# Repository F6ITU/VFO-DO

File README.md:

VFO-DO
RF Generator, Kicad project

VFO-DO est un générateur HF couvrant de quelques kHz à 100 MHz.

Il s'agit d'une idée originale de Gene Marcus W3PM/GM4YRE
publiée dans un article de la revue QEX

http://www.arrl.org/files/file/QEX_Next_Issue/2015/Jul-Aug_2015/Marcus.pdf

Ce projet Kicad n'est que la transposition dudit projet. 

La propriété intellectuelle et les droits de publication appartiennent respectivement 
à l'auteur et à la société de publication mentionnés

Ce projet Kicad poursuit deux buts : 

- offrir à chaque débutant en électronique ou en radioélectricité les éléments nécessaires
à la construction d'une source de fréquence excessivement stable (précise au Herz près, puisque pilotée par l'étalon césium
de l'essaim de satellites GPS)... et surtout simple à construire -à assembler serait le terme le plus exact.

- étendre cette réalisation, après modification du firmware, avec un filtre 

https://github.com/F6ITU/FiltreU

commuté de 8 bandes 

https://github.com/F6ITU/octorelay

qui éliminera en grande partie les harmoniques du générateur -lequel génère des signaux carrés-

De cette manière, la pureté spectrale est largement suffisante pour satisfaire la majorité des 
débutants en électronique "haute fréquence"

Le filtre n'est absolument pas nécessaire si l'oscillateur est utilisé en guise de VFO, surtout dans 
le cadre d'un mélangeur Tayloe ou assimilé. 

Cette réalisation peut également servir d'équipement de terrain, là ou le déplacement d'un oscillateur asservi
-équipement fragile et coûteux- est inenvisageable.

Plus d'informations sur le module oscillateur à base de SiLabs Si5351 
https://learn.adafruit.com/adafruit-si5351-clock-generator-breakout?view=all

une seconde source de ce module 

https://www.sv1afn.com/si5351a.html
Attention : ce dernier module n'est pas "pin compatible" avec le précédent

Le firmware originel de l'auteur 
http://www.knology.net/~gmarcus/Si5351/Si5351_vfo_v5.ino.zip

Un émetteur-récepteur WSPR conçu par l'auteur et utilisant ledit VFO-DO
http://www.knology.net/~gmarcus/Si5351/Si5351A_WSPR_XCVR.pdf

NB : le coût du générateur gravite aux environ des 30 euros, le filtre se situant peu ou prou dans la 
même zone de prix une fois tous les composants achetés. Cela fait oublier le bruit de phase
de l'oscillateur, lequel est assez catastrophique, surtout si on le compare à celui d'un OCXO ou 
TCXO.

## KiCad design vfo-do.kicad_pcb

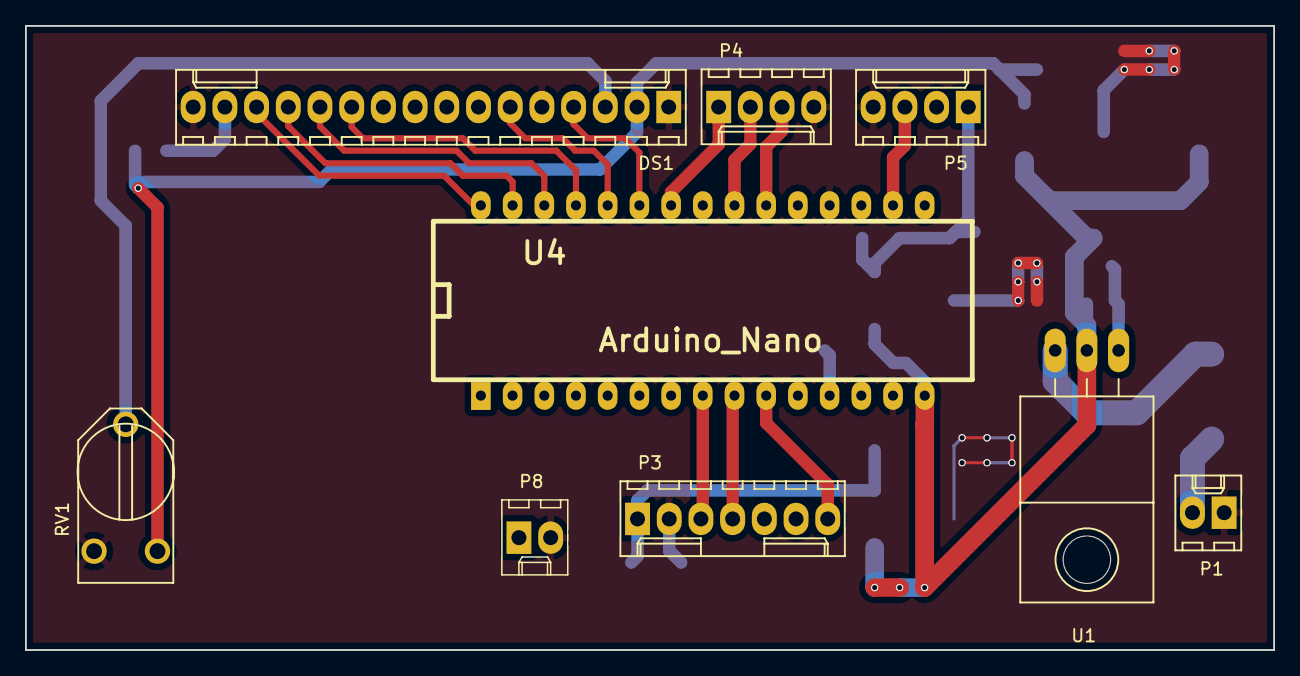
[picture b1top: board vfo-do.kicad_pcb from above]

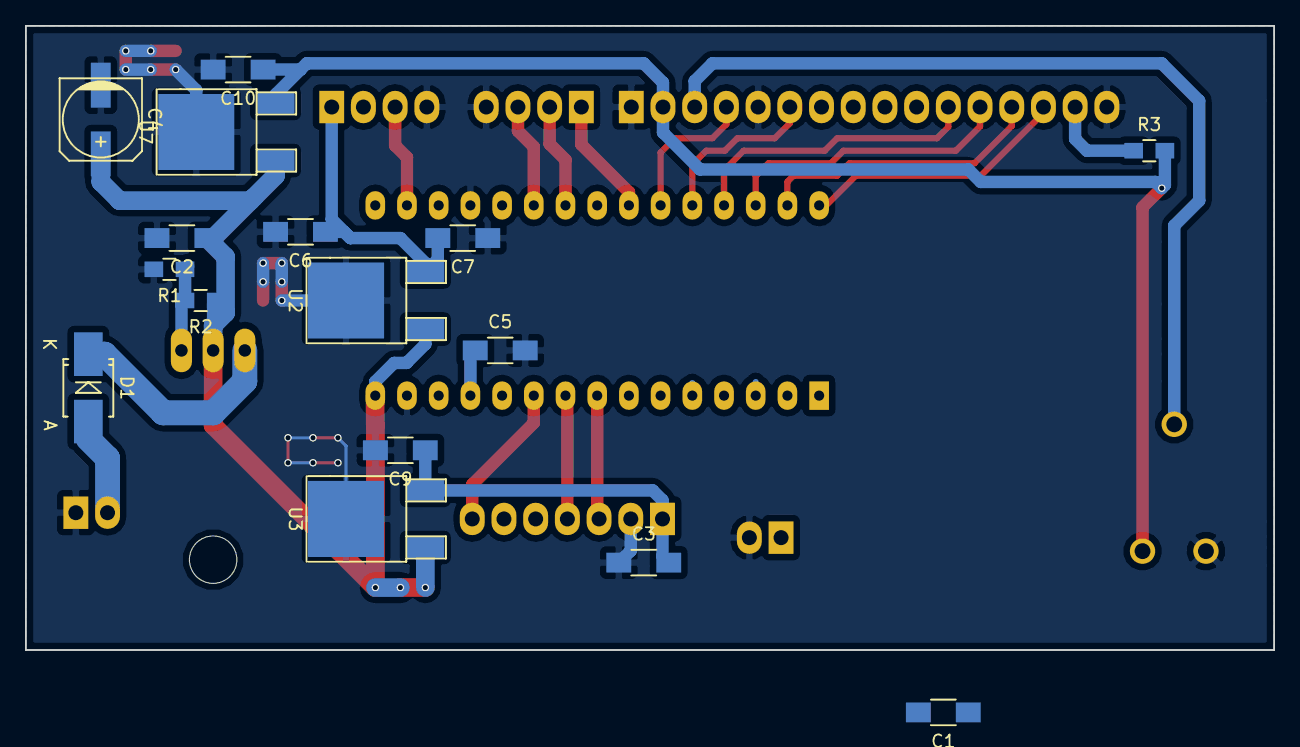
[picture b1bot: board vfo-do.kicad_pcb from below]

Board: 2 copper layers, 100.0 x 50.0 mm, 25 parts (16 on the bottom side), 26 nets.

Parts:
C1, C2, C3, C5, C6, C7, C9, C10: 100n; C_1206_HandSoldering
C4: 1500uF; c_elec_6.3x7.7
D1: D_Schottky; SMB_Handsoldering
DS1: LCD16X2; Molex_KK_6410-16
P1: CONN_01X02; Molex_KK_6410-02
P3: Si5351; Molex_KK_6410-07
P4: Encoder; Molex_KK_6410-04
P5: GPS; Molex_KK_6410-04
P8: Reset; Molex_KK-6410-02_02x2.54mm_Straight
R1: 1300; C_0805_HandSoldering
R2: 240; C_0805_HandSoldering
R3: 330; C_0805_HandSoldering
RV1: 10k; RV2X4
U1: LM317T; TO-220_Neutral123_Horizontal_LargePads
U2, U3, U7: MC78M05CDT; TO-252-2Lead
U4: Arduino_Nano; arduino_nano

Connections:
+5C: C6.1, C7.2, P5.1, U2.3
+5P: C10.1, DS1.2, R3.2, RV1.3, U7.3
+8V: C2.1, C4.1, R2.1, U1.2, U2.1, U3.1, U4.15, U7.1
+12V: D1.2, P1.2
GND: C1.2, C2.2, C3.1, C4.2, C5.2, C6.2, C7.1, C9.2, C10.2, DS1.1, DS1.5, DS1.16, P1.1, P3.2, P4.4, P5.4, P8.2, R1.2, RV1.1, U2.2, U3.2, U4.14, U4.19, U7.2
unnamed: C1.1, D1.1, U1.3
unnamed: C3.2, C9.1, P3.1, U3.3
unnamed: C5.1, U4.12
unnamed: DS1.3, RV1.2
unnamed: DS1.4, U4.25
unnamed: DS1.6, U4.26
unnamed: DS1.11, U4.27
unnamed: DS1.12, U4.28
unnamed: DS1.13, U4.29
unnamed: DS1.14, U4.30
unnamed: DS1.15, R3.1
unnamed: P3.3, U4.8
unnamed: P3.4, U4.9
unnamed: P3.7, U4.23
unnamed: P4.1, U4.24
unnamed: P4.2, U4.22
unnamed: P4.3, U4.21
unnamed: P5.2, U4.20
unnamed: P5.3, U4.17
unnamed: P8.1, U4.18
unnamed: R1.1, R2.2, U1.1

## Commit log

2016-05-03 branche originelle du projet VFO-DO
2016-05-03 readme enrichi
2016-05-03 modif du rappel de masse d'un rétulateur 5V
2016-05-04 modif mineure sur un rappel de masse
2016-05-07 modifications mineurs
2017-05-02 suppression des sorties filtres
2017-05-02 nettoyage routage, LM317 et Si5351 non verifie
